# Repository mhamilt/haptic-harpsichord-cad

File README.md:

# Haptic Harpsichord CAD
Repository of CAD project files for the [Haptic Harpsichord](https://github.com/mhamilt/harpsichord-jack-tracking)

## Components

### QRE1113

- [QRE1113 Datasheet](https://www.mouser.in/datasheet/2/308/QRE1113-1121523.pdf)

|  |  |
| :----------------------------------------------------------------------------------------------------------------------------------------: | :----------------------------------------------------------------------------------------------------------------------------------------: |
|                     QRE1113 Dimension. Not that pin 1 should always have a chamfer on the corner to help identify it.                      |                                                               QRE1113 Pinout                                                               |

### Multiplexer

- Datasheet

### LEDs

- Datasheet

### Rotary

- Datasheet

### FRAM

- Datasheet

## Eagle 

### Automating EAGLE Commands

Below is python code used to generate commands that can be copy and pasted into EAGLE.

EAGLE has it's [ULP](https://web.mit.edu/xavid/arch/i386_rhel4/help/129.htm), but the intention here is to provide a light weight and easily modifiable system.

#### Faceboard

```py
qrepitch = 1.8 # placement is calculated from the #1 pin, pitch is used to offset to the centre
ox = 1.705     # min distance from board edge
oy = 1.705     # min distance from board edge in y axis
pitch = 14.02 # jack pitch
max_board_width = (6*pitch) + ox + qrepitch + ox

for index, point in enumerate([(x * pitch) + ox for x in range(0,7)]):
  print(f"move Q{index+1} ({oy} {point});")

resitor100k_ox = 10.1 # min distance from board edge in y axis
resitor100k_oy = 7.0 # min distance from board edge in y axis
resitor100_ox = 7.5 # min distance from board edge in y axis
resitor100_oy = 7.0 # min distance from board edge in y axis
rpitch = 12.9

for index, point in enumerate([(x * rpitch) + resitor100_oy for x in range(0,16)]):
  if index < 7:
    print(f"move R{(index*2)+1} ({resitor100_ox} {point});")
    print(f"move R{(index+1)*2} ({resitor10k_ox} {point});")
  if index >= 7:
    print(f"move R{((index+1)*2)+1} ({resitor100_ox} {point});")
    print(f"move R{((index+1)+1)*2} ({resitor10k_ox} {point});")

led_ox = 23.08 # min distance from board edge in x axis
led_ox = 23.68
# led_oy = 4.4 # min distance from board edge in y axis
# led_pitch = 12.0
led_pitch = 17.73 - 3.71
led_oy = 3.71 + (qrepitch/2) # min distance from board edge in y axis

for index, point in enumerate([(x * led_pitch) + led_oy for x in range(0,7)]):
  print(f"rotate D{(index+1)} 270;")
  print(f"move D{(7-index)} ({led_ox} {point});")
  print(f"mirror D{(index+1)};")

```

#### Sensor Board

```py
ox = 1.705         # mm min distance from board edge
oy = 1.705         # mm min distance from board edge in y axis
rotx = 3.55        # mm min x distance but for a 90 rotated sensor
jack_pitch = 14.02 # mm

led_ox = 23.08 # min distance from board edge in x axis
led_pitch = 17.73 - 3.71 # mini 3535 neopixels

for i, p in enumerate([(x * jack_pitch) + oy for x in range(0,7)]):
  print(f"ROTATE =R90 Q{i+1};")

for i, p in enumerate([(x * jack_pitch) + oy for x in range(0,7)]):
  print(f"move Q{i+1} ({rotx} {p});")

for i, p in enumerate([(x * led_pitch) + led_oy for x in range(0,7)]):
  print(f"ROTATE =R90 LED{i+1};")

for index, point in enumerate([(x * led_pitch) + led_oy for x in range(0,7)]):  
  print(f"move LED{(index+1)} ({led_ox} {point});")

for index, point in enumerate([(x * led_pitch) + led_oy for x in range(0,7)]):  
  print(f"mirror LED{(index+1)};")

```

#### Sensor Board SMD

```py
ox = 1.705         # mm min distance from board edge
oy = 1.705         # mm min distance from board edge in y axis
rotx = 3.55        # mm min x distance but for a 90 rotated sensor
jack_pitch = 14.02 # mm

led_ox = 23.08 # min distance from board edge in x axis
led_pitch = 17.73 - 3.71 # mini 3535 neopixels

for i, p in enumerate([(x * jack_pitch) + oy for x in range(0,7)]):
  print(f"ROTATE =R90 Q{i+1};")

for i, point in enumerate([(x * jack_pitch) + ox for x in range(0,7)]):
  print(f"move Q{i+1} ({oy} {p});")

for i, p in enumerate([(x * led_pitch) + led_oy for x in range(0,7)]):
  print(f"ROTATE =R90 LED{i+1};")

for i, p in enumerate([(x * led_pitch) + led_oy for x in range(0,7)]):  
  print(f"move LED{(i+1)} ({led_ox} {point});")

for i, p in enumerate([(x * led_pitch) + led_oy for x in range(0,7)]):  
  print(f"mirror LED{(i+1)};")

```

## Mount Holes

### Sensor Board

```
Mount Holes: (4.5 81.5), (4.5 11) 
```
### Signal Board

```
Mount Holes: (12.5 75), (12.5 18) 
```

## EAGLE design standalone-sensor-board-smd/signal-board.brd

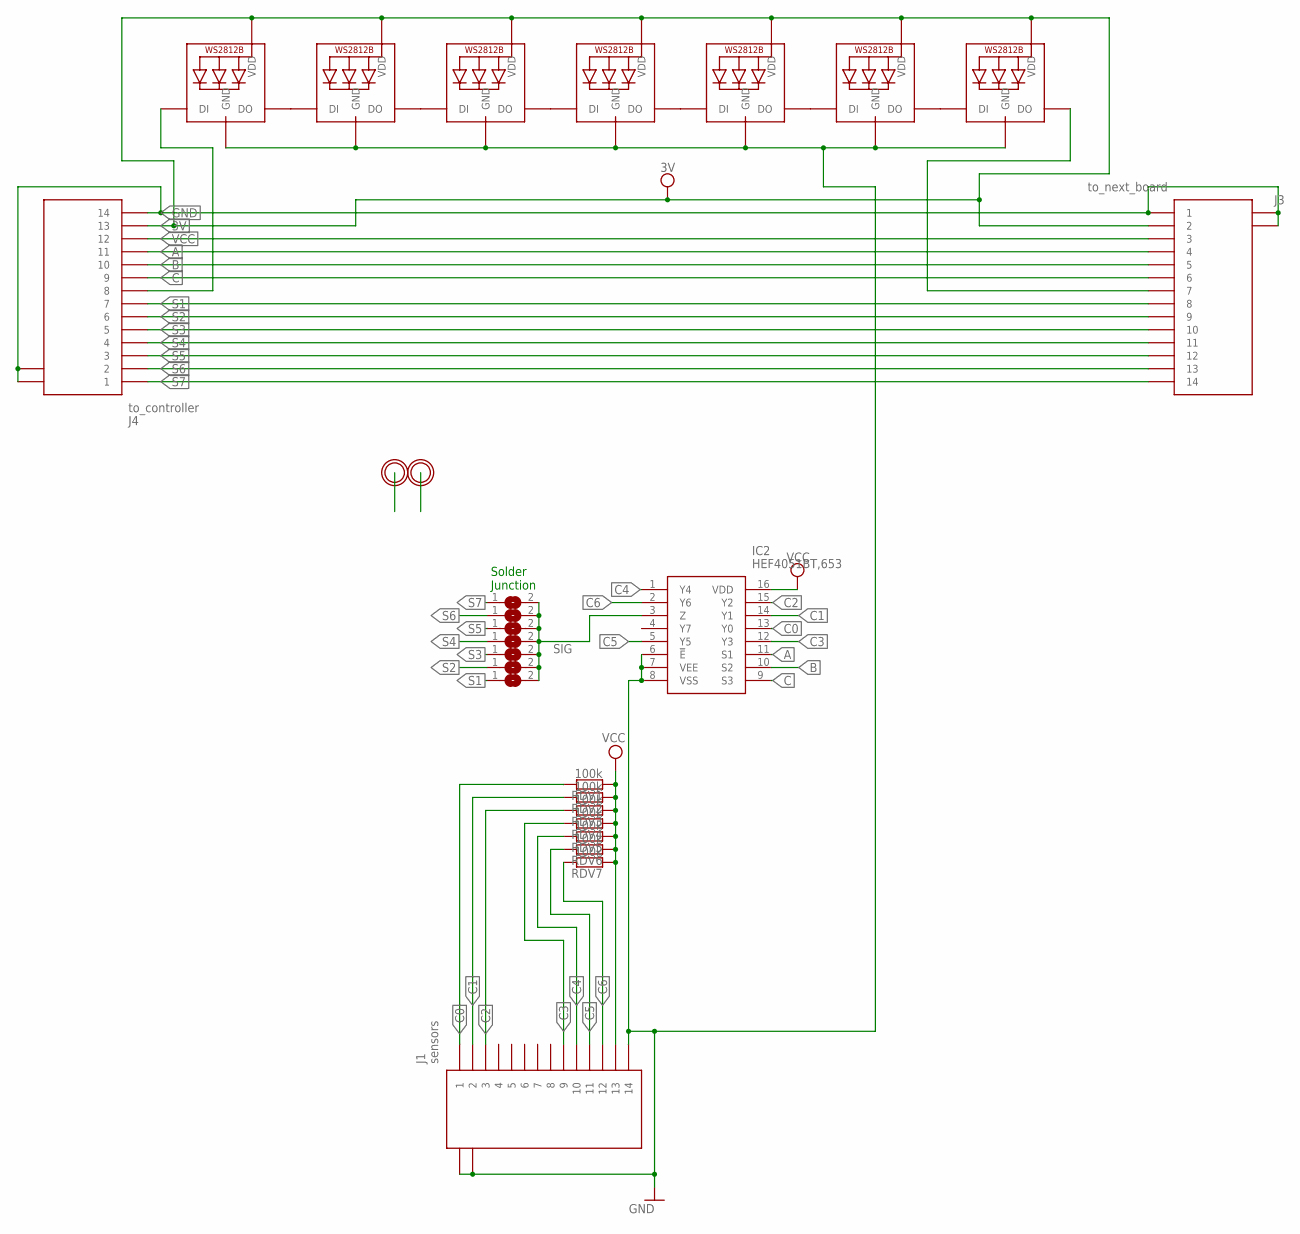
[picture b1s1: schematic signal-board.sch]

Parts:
IC2: HEF4051BT,653; HEF4051BT653
J1: sensors; 686114148922
J3: to_next_board; 686114148922
J4: to_controller; 686114148922
LED1, LED2, LED3, LED4, LED5, LED6, LED7: WS2812B3535; LED3535
RDV1, RDV2, RDV3, RDV4, RDV5, RDV6, RDV7: 100k; R0805
SJ1, SJ2, SJ3, SJ4, SJ5, SJ6, SJ7: SJ
U$1, U$2: MICROBUILDER_MOUNTINGHOLEMICROBUILDER_MOUNTINGHOL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; MICROBUILDER_MOUNTINGHOLE_4.0_PLATEDTHIN

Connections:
3V: J3.2, J4.13, LED1.2 (VDD), LED2.2 (VDD), LED3.2 (VDD), LED4.2 (VDD), LED5.2 (VDD), LED6.2 (VDD), LED7.2 (VDD)
A: IC2.11 (S1), J3.4, J4.11
B: IC2.10 (S2), J3.5, J4.10
C: IC2.9 (S3), J3.6, J4.9
C0: IC2.13 (Y0), J1.1, RDV1.2
C1: IC2.14 (Y1), J1.2, RDV2.2
C2: IC2.15 (Y2), J1.3, RDV3.2
C3: IC2.12 (Y3), J1.9, RDV4.2
C4: IC2.1 (Y4), J1.10, RDV5.2
C5: IC2.5 (Y5), J1.11, RDV6.2
C6: IC2.2 (Y6), J1.12, RDV7.2
DIN: J4.8, LED1.1 (DI)
DOUT: J3.7, LED7.3 (DO)
GND: IC2.6 (!E), IC2.7 (VEE), IC2.8 (VSS), J1.14, J1.MP1, J1.MP2, J3.1, J3.MP1, J3.MP2, J4.14, J4.MP1, J4.MP2, LED1.4 (GND), LED2.4 (GND), LED3.4 (GND), LED4.4 (GND), LED5.4 (GND), LED6.4 (GND), LED7.4 (GND)
unnamed: LED1.3 (DO), LED2.1 (DI)
unnamed: LED2.3 (DO), LED3.1 (DI)
unnamed: LED3.3 (DO), LED4.1 (DI)
unnamed: LED4.3 (DO), LED5.1 (DI)
unnamed: LED5.3 (DO), LED6.1 (DI)
unnamed: LED6.3 (DO), LED7.1 (DI)
S1: J3.8, J4.7, SJ1.1
S2: J3.9, J4.6, SJ2.1
S3: J3.10, J4.5, SJ3.1
S4: J3.11, J4.4, SJ4.1
S5: J3.12, J4.3, SJ5.1
S6: J3.13, J4.2, SJ6.1
S7: J3.14, J4.1, SJ7.1
SIG: IC2.3 (Z), SJ1.2, SJ2.2, SJ3.2, SJ4.2, SJ5.2, SJ6.2, SJ7.2
VCC: IC2.16 (VDD), J1.13, J3.3, J4.12, RDV1.1, RDV2.1, RDV3.1, RDV4.1, RDV5.1, RDV6.1, RDV7.1

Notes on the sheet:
Solder Junction

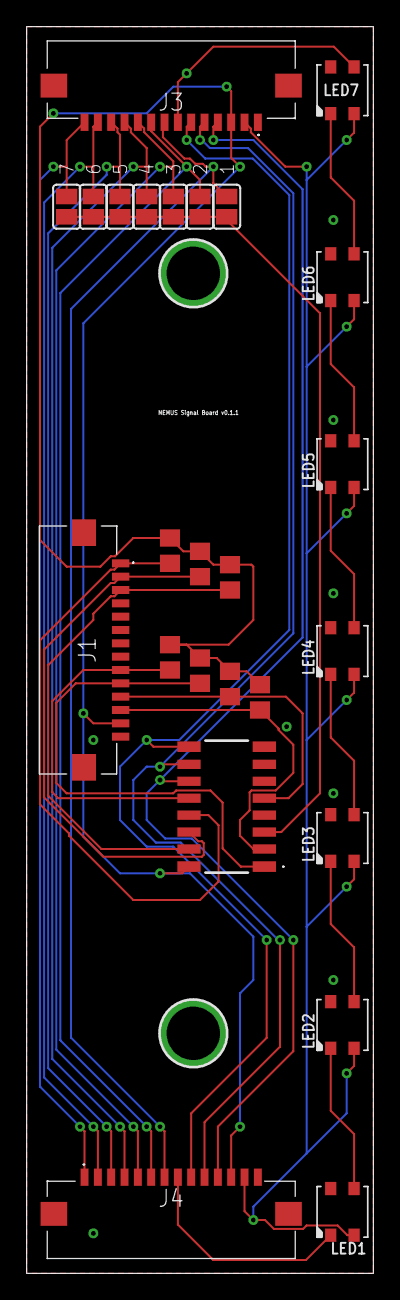
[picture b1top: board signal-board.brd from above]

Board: 2 copper layers, 26.0 x 93.5 mm, 27 parts (0 on the bottom side), 29 nets.

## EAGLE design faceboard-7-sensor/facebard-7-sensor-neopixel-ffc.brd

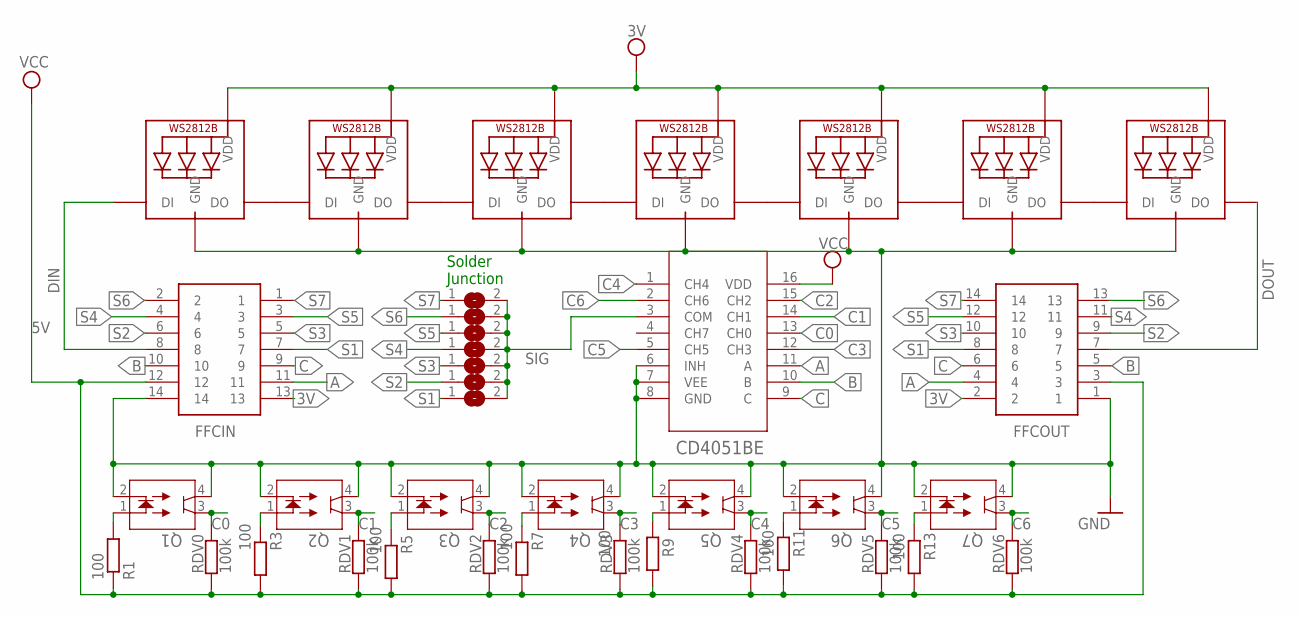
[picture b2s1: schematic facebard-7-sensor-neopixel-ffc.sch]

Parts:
FFCIN: 52806-1410; 528061410
FFCOUT: 52806-1410; 528061410
LED1, LED2, LED3, LED4, LED5, LED6, LED7: WS2812B3535; LED3535
Q1, Q2, Q3, Q4, Q5, Q6, Q7: QRE1113; DIP4_100AQ_ONS
R1, R3, R5, R7, R9, R11, R13: 100; 0207/10
RDV0, RDV1, RDV2, RDV3, RDV4, RDV5, RDV6: 100k; 0207/10
SJ1, SJ2, SJ3, SJ4, SJ5, SJ6, SJ7: SJ
U1: CD4051BE; N16

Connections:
3V: FFCIN.13, FFCOUT.2, LED1.2 (VDD), LED2.2 (VDD), LED3.2 (VDD), LED4.2 (VDD), LED5.2 (VDD), LED6.2 (VDD), LED7.2 (VDD)
5V: FFCIN.12, FFCOUT.3, R1.1, R3.1, R5.1, R7.1, R9.1, R11.1, R13.1, RDV0.1, RDV1.1, RDV2.1, RDV3.1, RDV4.1, RDV5.1, RDV6.1, U1.16 (VDD)
A: FFCIN.11, FFCOUT.4, U1.11 (A)
B: FFCIN.10, FFCOUT.5, U1.10 (B)
C: FFCIN.9, FFCOUT.6, U1.9 (C)
C0: Q1.3, RDV0.2, U1.13 (CH0)
C1: Q2.3, RDV1.2, U1.14 (CH1)
C2: Q3.3, RDV2.2, U1.15 (CH2)
C3: Q4.3, RDV3.2, U1.12 (CH3)
C4: Q5.3, RDV4.2, U1.1 (CH4)
C5: Q6.3, RDV5.2, U1.5 (CH5)
C6: Q7.3, RDV6.2, U1.2 (CH6)
DIN: FFCIN.8, LED1.1 (DI)
DOUT: FFCOUT.7, LED7.3 (DO)
GND: FFCIN.14, FFCOUT.1, LED1.4 (GND), LED2.4 (GND), LED3.4 (GND), LED4.4 (GND), LED5.4 (GND), LED6.4 (GND), LED7.4 (GND), Q1.2, Q1.4, Q2.2, Q2.4, Q3.2, Q3.4, Q4.2, Q4.4, Q5.2, Q5.4, Q6.2, Q6.4, Q7.2, Q7.4, U1.6 (INH), U1.7 (VEE), U1.8 (GND)
unnamed: Q1.1, R1.2
unnamed: Q2.1, R3.2
unnamed: LED1.3 (DO), LED2.1 (DI)
unnamed: Q3.1, R5.2
unnamed: LED2.3 (DO), LED3.1 (DI)
unnamed: Q4.1, R7.2
unnamed: LED3.3 (DO), LED4.1 (DI)
unnamed: LED4.3 (DO), LED5.1 (DI)
unnamed: LED5.3 (DO), LED6.1 (DI)
unnamed: Q6.1, R11.2
unnamed: LED6.3 (DO), LED7.1 (DI)
unnamed: Q7.1, R13.2
unnamed: Q5.1, R9.2
S1: FFCIN.7, FFCOUT.8, SJ1.1
S2: FFCIN.6, FFCOUT.9, SJ2.1
S3: FFCIN.5, FFCOUT.10, SJ3.1
S4: FFCIN.4, FFCOUT.11, SJ4.1
S5: FFCIN.3, FFCOUT.12, SJ5.1
S6: FFCIN.2, FFCOUT.13, SJ6.1
S7: FFCIN.1, FFCOUT.14, SJ7.1
SIG: SJ1.2, SJ2.2, SJ3.2, SJ4.2, SJ5.2, SJ6.2, SJ7.2, U1.3 (COM)

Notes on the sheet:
Solder Junction

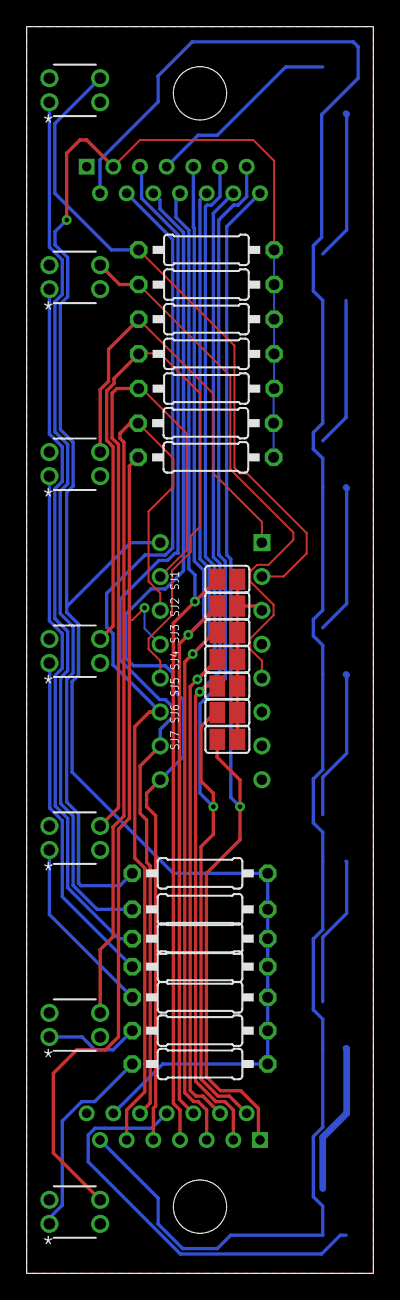
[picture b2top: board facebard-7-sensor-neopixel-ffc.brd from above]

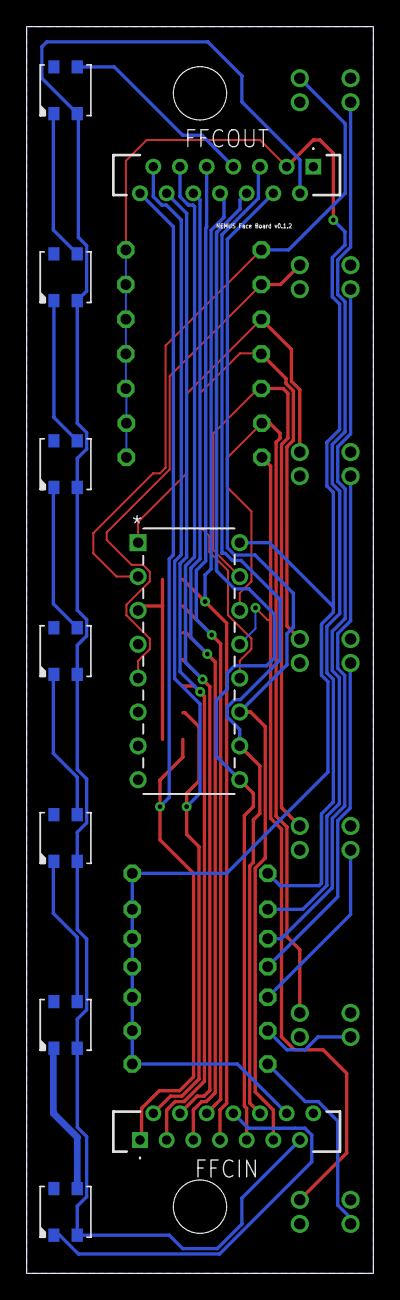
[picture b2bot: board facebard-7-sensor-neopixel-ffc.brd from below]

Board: 2 copper layers, 26.0 x 93.5 mm, 38 parts (10 on the bottom side), 36 nets.

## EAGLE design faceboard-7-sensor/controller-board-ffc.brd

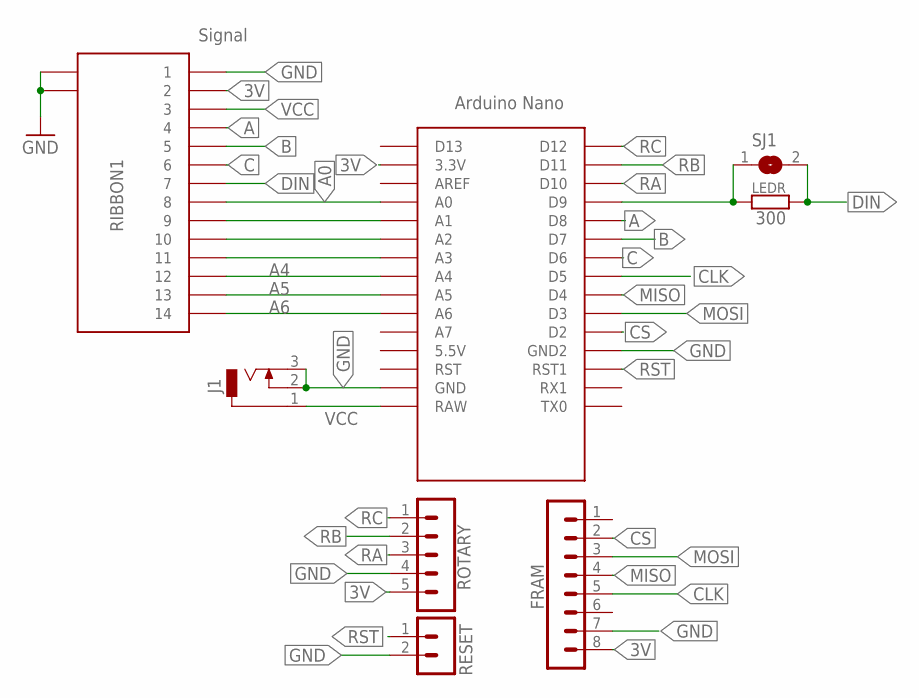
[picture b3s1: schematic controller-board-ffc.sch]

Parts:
FRAM: MB85RS2MTA; MA08-1
J1: DCJ0202
LEDR: 300; 0207/10
RESET: B2B-PH-K
RIBBON1: Signal; 686114148922
ROTARY: B5B-PH-K
SJ1: SJ
U$1: NANO

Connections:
3V: FRAM.8, RIBBON1.2, ROTARY.5, U$1.3.3V
A: RIBBON1.4, U$1.D8
A0: RIBBON1.8, U$1.A0
A1: RIBBON1.9, U$1.A1
A2: RIBBON1.10, U$1.A2
A3: RIBBON1.11, U$1.A3
A4: RIBBON1.12, U$1.A4
A5: RIBBON1.13, U$1.A5
A6: RIBBON1.14, U$1.A6
B: RIBBON1.5, U$1.D7
C: RIBBON1.6, U$1.D6
CLK: FRAM.5, U$1.D5
CS: FRAM.2, U$1.D2
D9: LEDR.1, SJ1.1, U$1.D9
DIN: LEDR.2, RIBBON1.7, SJ1.2
GND: FRAM.7, J1.2, J1.3, RESET.2, RIBBON1.1, RIBBON1.MP1, RIBBON1.MP2, ROTARY.4, U$1.GND, U$1.GND1 (GND2)
MISO: FRAM.4, U$1.D4
MOSI: FRAM.3, U$1.D3
RA: ROTARY.3, U$1.D10
RB: ROTARY.2, U$1.D11
RC: ROTARY.1, U$1.D12
RST: RESET.1, U$1.RST1
VCC: J1.1, RIBBON1.3, U$1.RAW

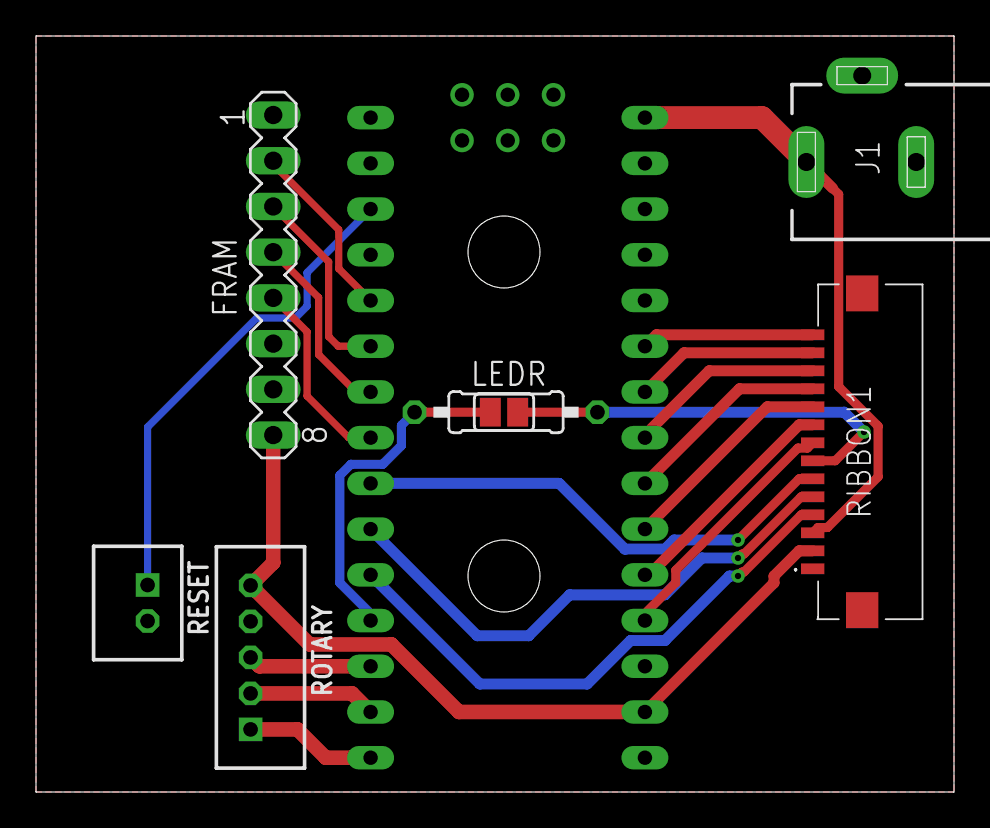
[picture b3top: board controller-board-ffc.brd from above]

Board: 2 copper layers, 51.0 x 42.0 mm, 8 parts (0 on the bottom side), 23 nets.

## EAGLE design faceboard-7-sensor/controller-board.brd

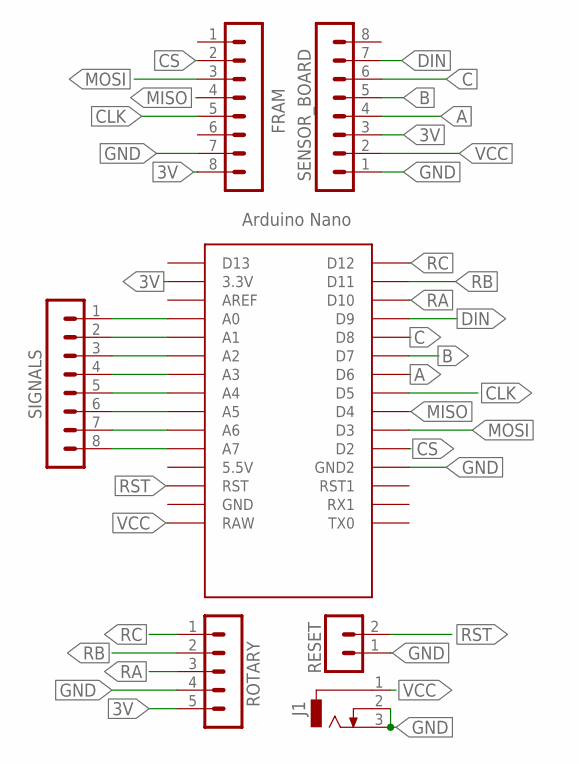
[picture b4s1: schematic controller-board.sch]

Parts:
ANALOG: SIGNALS; MA08-1
FRAM: FRAM; MA08-1
J1: DCJ0202
RESET: B2B-PH-K
ROTARY: B5B-PH-K
SV2: SENSOR_BOARD; MA08-1
U$1: NANO

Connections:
3V: FRAM.8, ROTARY.5, SV2.3, U$1.3.3V
A: SV2.4, U$1.D6
A0: ANALOG.1, U$1.A0
A1: ANALOG.2, U$1.A1
A2: ANALOG.3, U$1.A2
A3: ANALOG.4, U$1.A3
A4: ANALOG.5, U$1.A4
A5: ANALOG.6, U$1.A5
A6: ANALOG.7, U$1.A6
A7: ANALOG.8, U$1.A7
B: SV2.5, U$1.D7
C: SV2.6, U$1.D8
CLK: FRAM.5, U$1.D5
CS: FRAM.2, U$1.D2
DIN: SV2.7, U$1.D9
GND: FRAM.7, J1.2, J1.3, RESET.1, ROTARY.4, SV2.1, U$1.GND1 (GND2)
MISO: FRAM.4, U$1.D4
MOSI: FRAM.3, U$1.D3
RA: ROTARY.3, U$1.D10
RB: ROTARY.2, U$1.D11
RC: ROTARY.1, U$1.D12
RST: RESET.2, U$1.RST
VCC: J1.1, SV2.2, U$1.RAW

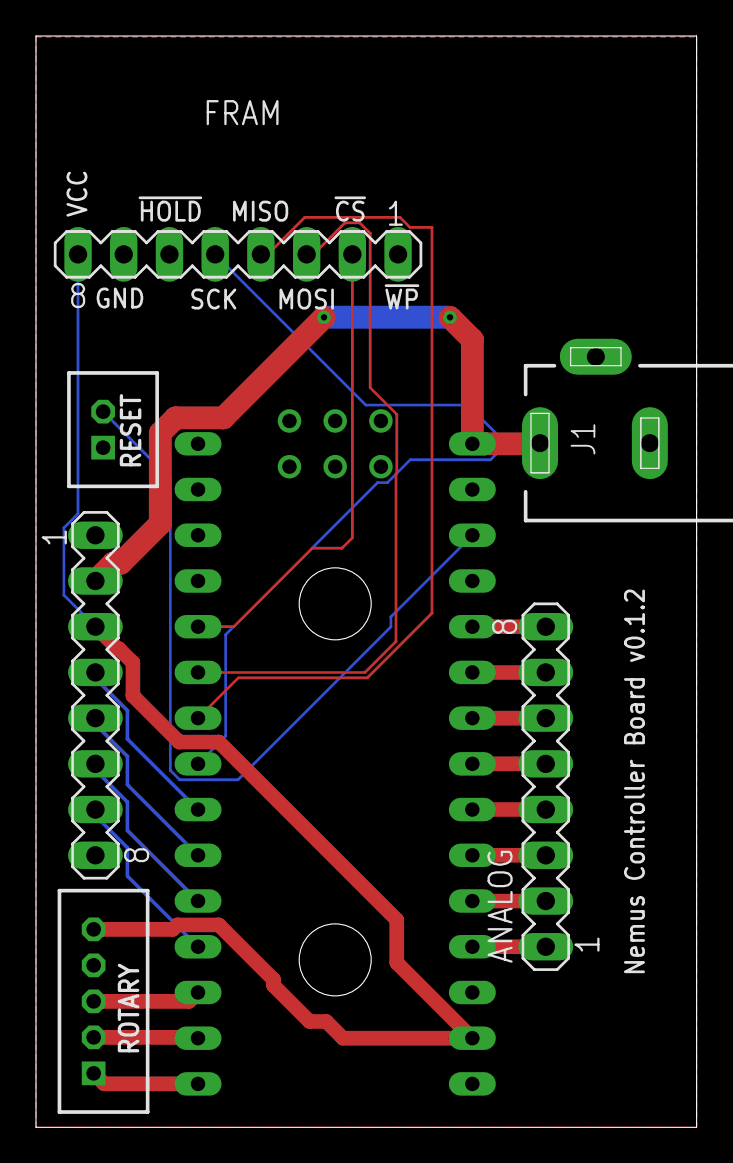
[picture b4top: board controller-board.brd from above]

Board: 2 copper layers, 36.7 x 60.6 mm, 7 parts (0 on the bottom side), 23 nets.

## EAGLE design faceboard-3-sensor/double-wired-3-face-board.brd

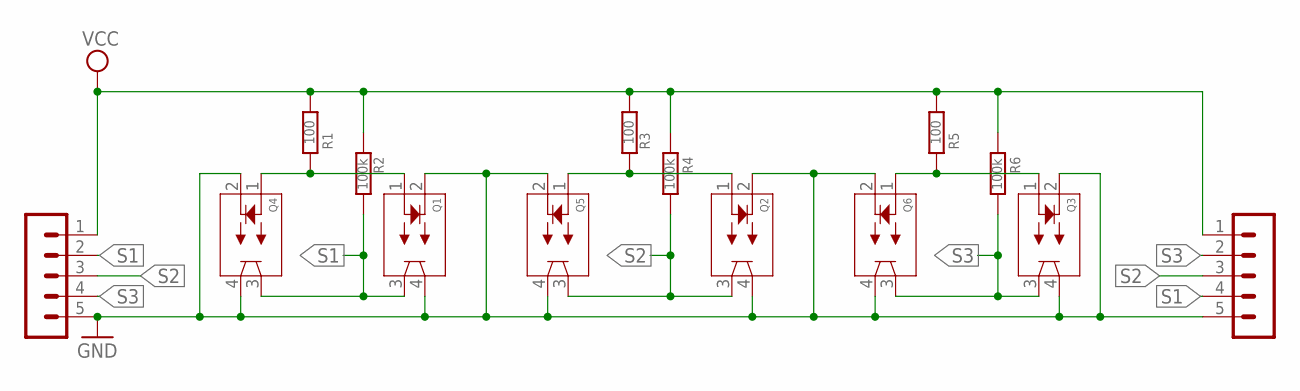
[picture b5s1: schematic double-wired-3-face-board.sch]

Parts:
Q1, Q2, Q3, Q4, Q5, Q6: QRE1113; DIP4_100AQ_ONS
R1, R3, R5: 100; 0207/10
R2, R4, R6: 100k; 0207/10
SV1, SV2: on; MA05-1

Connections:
5VQ1: Q1.1, Q4.1, R1.2
5VQ2: Q2.1, Q5.1, R3.2
5VQ3: Q3.1, Q6.1, R5.2
GND: Q1.2, Q1.4, Q2.2, Q2.4, Q3.2, Q3.4, Q4.2, Q4.4, Q5.2, Q5.4, Q6.2, Q6.4, SV1.5, SV2.5
S1: Q1.3, Q4.3, R2.1, SV1.4, SV2.2
S2: Q2.3, Q5.3, R4.1, SV1.3, SV2.3
S3: Q3.3, Q6.3, R6.1, SV1.2, SV2.4
VCC: R1.1, R2.2, R3.1, R4.2, R5.1, R6.2, SV1.1, SV2.1

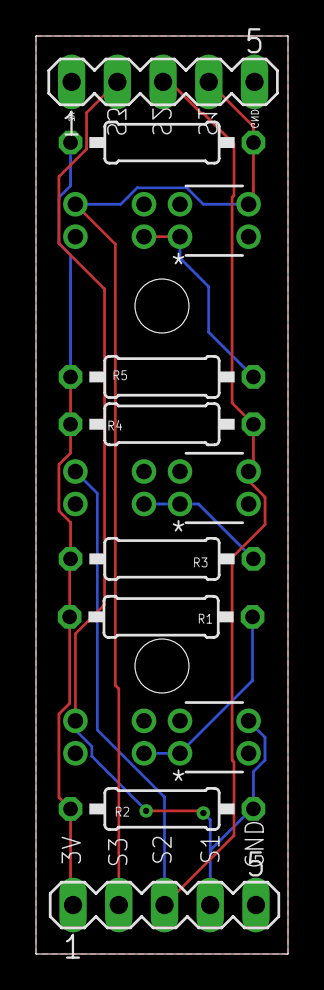
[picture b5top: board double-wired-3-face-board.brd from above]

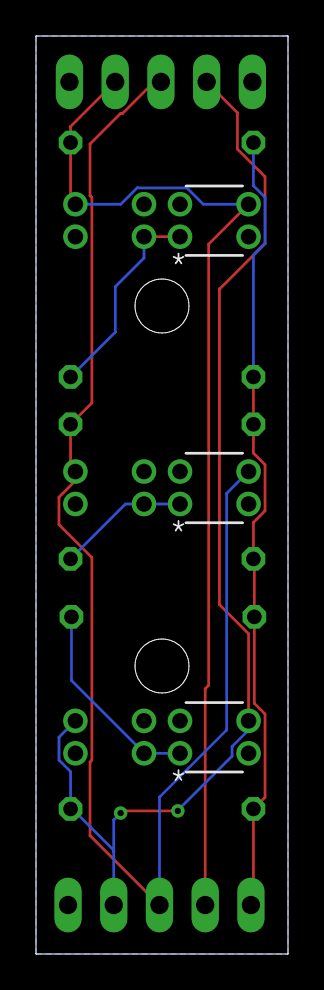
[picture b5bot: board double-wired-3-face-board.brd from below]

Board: 2 copper layers, 14.0 x 51.0 mm, 14 parts (3 on the bottom side), 8 nets.

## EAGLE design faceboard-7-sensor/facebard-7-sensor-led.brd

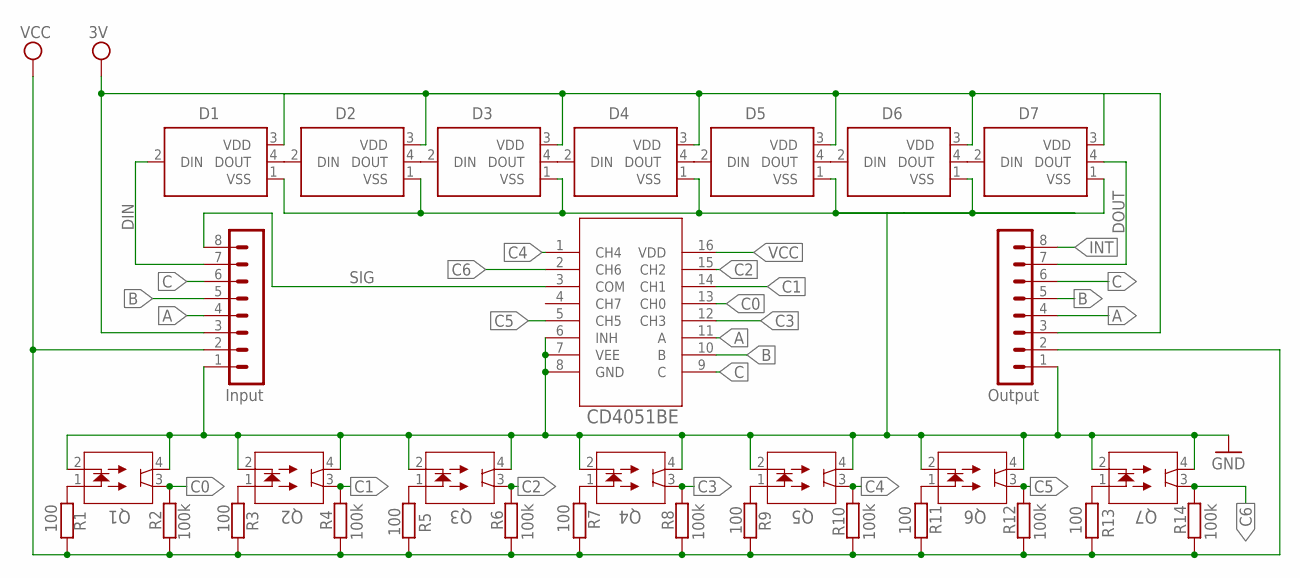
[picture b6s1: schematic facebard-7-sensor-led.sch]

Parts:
D1, D2, D3, D4, D5, D6, D7: 1655; LED_1655
Q1, Q2, Q3, Q4, Q5, Q6, Q7: QRE1113; DIP4_100AQ_ONS
R1, R3, R5, R7, R9, R11, R13: 100; 0207/10
R2, R4, R6, R8, R10, R12, R14: 100k; 0207/10
SV2: Output; MA08-1
SV3: Input; MA08-1
U1: CD4051BE; N16

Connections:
3V: D1.3 (VDD), D2.3 (VDD), D3.3 (VDD), D4.3 (VDD), D5.3 (VDD), D6.3 (VDD), D7.3 (VDD), SV2.3, SV3.3
A: SV2.4, SV3.4, U1.11 (A)
B: SV2.5, SV3.5, U1.10 (B)
C: SV2.6, SV3.6, U1.9 (C)
C0: Q1.3, R2.1, U1.13 (CH0)
C1: Q2.3, R4.1, U1.14 (CH1)
C2: Q3.3, R6.1, U1.15 (CH2)
C3: Q4.3, R8.1, U1.12 (CH3)
C4: Q5.3, R10.1, U1.1 (CH4)
C5: Q6.3, R12.1, U1.5 (CH5)
C6: Q7.3, R14.1, U1.2 (CH6)
DIN: D1.2 (DIN), SV3.7
DOUT: D7.4 (DOUT), SV2.7
GND: D5.1 (VSS), D6.1 (VSS), D7.1 (VSS), Q1.2, Q1.4, Q2.2, Q2.4, Q3.2, Q3.4, Q4.2, Q4.4, Q5.2, Q5.4, Q6.2, Q6.4, Q7.2, Q7.4, SV2.1, SV3.1, U1.6 (INH), U1.7 (VEE), U1.8 (GND)
INT: SV2.8
unnamed: Q1.1, R1.2
unnamed: D6.4 (DOUT), D7.2 (DIN)
unnamed: Q2.1, R3.2
unnamed: D5.4 (DOUT), D6.2 (DIN)
unnamed: Q3.1, R5.2
unnamed: D2.4 (DOUT), D3.2 (DIN)
unnamed: Q4.1, R7.2
unnamed: D3.4 (DOUT), D4.2 (DIN)
unnamed: Q5.1, R9.2
unnamed: D4.4 (DOUT), D5.2 (DIN)
unnamed: Q6.1, R11.2
unnamed: Q7.1, R13.2
unnamed: D1.1 (VSS), D2.1 (VSS), D3.1 (VSS)
unnamed: D1.4 (DOUT), D2.2 (DIN)
SIG: SV3.8, U1.3 (COM)
VCC: R1.1, R2.2, R3.1, R4.2, R5.1, R6.2, R7.1, R8.2, R9.1, R10.2, R11.1, R12.2, R13.1, R14.2, SV2.2, SV3.2, U1.16 (VDD)

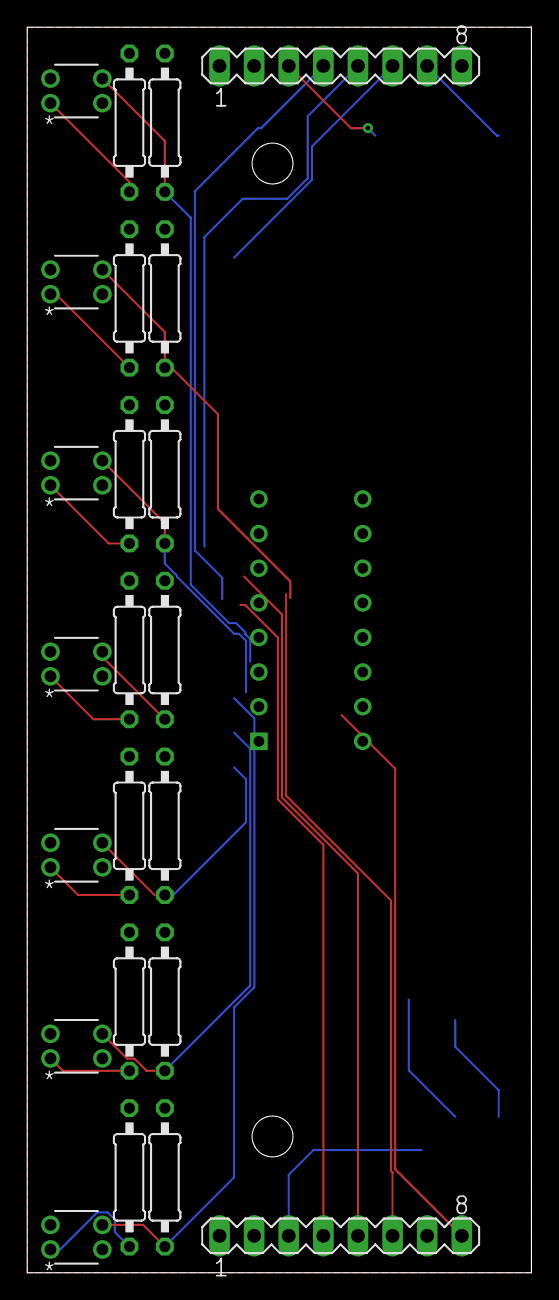
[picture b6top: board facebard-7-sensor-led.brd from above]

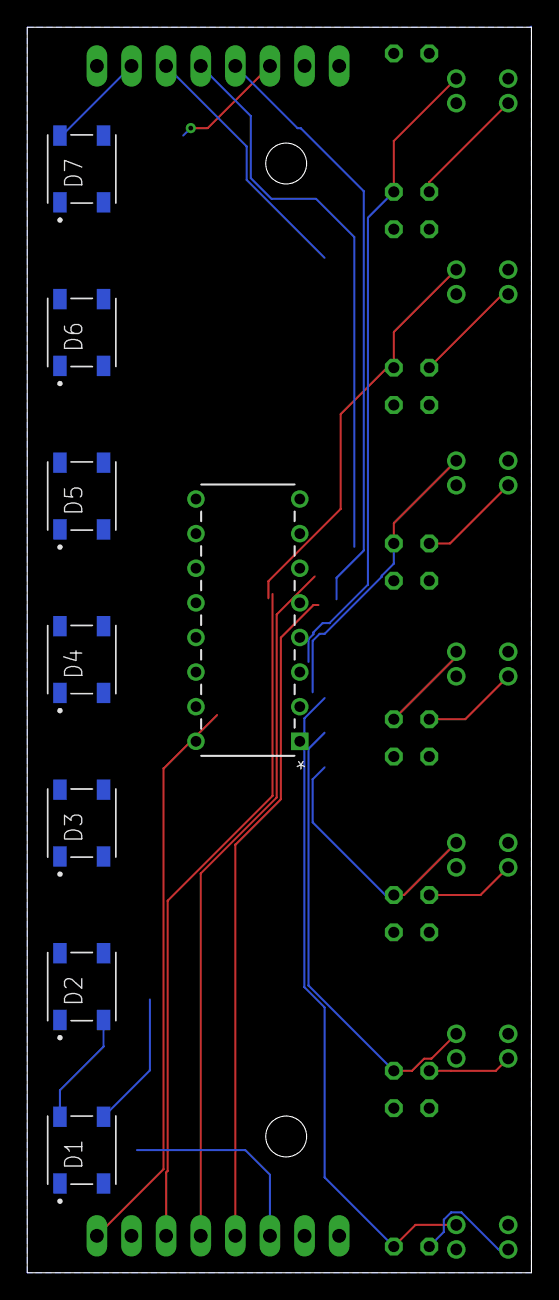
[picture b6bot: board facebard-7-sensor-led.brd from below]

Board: 2 copper layers, 37.0 x 91.4 mm, 31 parts (8 on the bottom side), 30 nets.

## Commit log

2024-11-06 init
2024-11-06 add original LED board
2024-11-06 add bracket `.stl` files
2024-11-11 add ffc
2024-11-11 remove 0.5mm ffc
2024-11-21 add ffc boards
2024-12-03 add components section
2025-01-07 tidy labelling
2025-07-24 add bom
2025-07-24 tidy routing
2025-07-24 routing
2025-07-24 update divide resistor value
2025-07-24 change divide resistor value
2025-07-24 tidy connections
2025-08-26 re-draw schematics
2025-08-26 fix vcc net
2025-08-26 add din dout labels
2025-08-26 add sig label
2025-08-26 redraw schematics
2025-12-12 add miniboard
2025-12-12 init standalone design
2025-12-12 tidy
2025-12-12 sensor board
2025-12-12 route
2025-12-12 init smd version
2025-12-12 rough layout
2025-12-12 init smd
2025-12-12 add dependant part libraries
2026-01-17 reroute
2026-01-17 rewire mini leds and dividing resistors
2026-01-17 fix signal routing
2026-01-17 add smd board
2026-01-17 add divider resistors
2026-01-20 set rdvs
2026-01-20 add smd boards from standalone
2026-01-20 sensor board routing
2026-01-20 signal board routing
2026-01-20 add smd mux lib
2026-01-20 add mounting holes
2026-01-21 clear out old boards
2026-01-21 tidy silk screen
2026-01-21 set GND
2026-01-21 add version labels
2026-01-21 fix version number
2026-01-21 tidy layers

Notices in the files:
parts and their libraries:
COPYRIGHT: Copyright (C) 2024 Ultra Librarian. All rights reserved.
con-jst-ph: Copyright (C) 2016, Bob Starr
